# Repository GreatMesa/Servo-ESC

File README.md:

# Servo-ESC
Custom 4-Layer Board for better servo control.
Mainly uses I2C for IC communication & the analog pheripherials on the STM32F301
## Overview
This project stems from the want to replace the boards that normally control position on commercial servos.

The reason why I wanted to replace them is because 1, you can only control the position of the servo motors and not the velocity, let alone the torque. Also, you cannot get any useful feedback back from the servos, which means that you cannot get the current or temperature of the board, which could be useful for looking at possible faults / seeing the current overall power consumption.

With these Servo ESC's, you can communicate to the board using I2C, which allows to send the wanted position, velocity, and torque, while also communicating back the current position, velocity, torque, power consumption, and board temperature. This allows for a much higher view into what is happening in the board while also giving the servo greater precision.

## Board Schematic

## PCB Layout

## 3D Model

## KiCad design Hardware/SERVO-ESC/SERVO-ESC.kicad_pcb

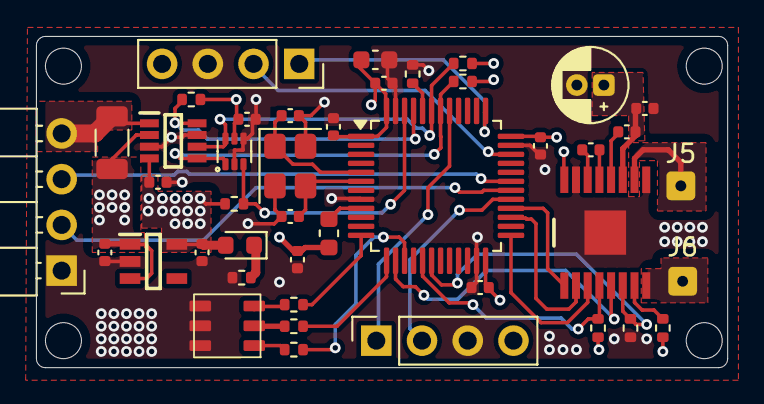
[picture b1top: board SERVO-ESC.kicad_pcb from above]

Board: 4 copper layers, 38.4 x 18.4 mm, 43 parts (0 on the bottom side), 37 nets.

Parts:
C1, C2, C3, C4, C9, C10, C15: 100nF; C_0402_1005Metric
C5: 4.7uF; C_0603_1608Metric
C6, C8, C12: 1uF; C_0402_1005Metric
C7: 22nF; C_0402_1005Metric
C11: 22uF; CP_Radial_D4.0mm_P1.50mm
C13, C14: 30pF; C_0402_1005Metric
C16: 10nF; C_0402_1005Metric
D1: LED; LED_0603_1608Metric
FB1: FerriteBead; L_0603_1608Metric
IC1: AP2112K; SOT95P285X140-5N
IC2: DRV8876PWPR; SOP65P640X120-17N
IC4: TMP102xxDRL; SOT-563
IC5: INA236AIDDFR; SOP65P280X110-8N
J1: Conn_01x04_Pin; PinHeader_1x04_P2.54mm_Horizontal
J2, J4: Conn_01x04_Pin; PinSocket_1x04_P2.54mm_Vertical
J5: +; SolderWire-0.1sqmm_1x01_D0.4mm_OD1mm
J6: -; SolderWire-0.1sqmm_1x01_D0.4mm_OD1mm
LED1: Untitled_1
R1, R10: 10k; R_0402_1005Metric
R2, R3, R4: 220; R_0402_1005Metric
R5, R6, R12, R13: 4.7k; R_0402_1005Metric
R7: 1k; R_0402_1005Metric
R8: 62k; R_0402_1005Metric
R9: 8.25k; R_0402_1005Metric
R11: 0.01; R_1206_3216Metric
U1: STM32F301C8Tx; LQFP-48_7x7mm_P0.5mm
Y1: 25MHZ; Crystal_SMD_3225-4Pin_3.2x2.5mm

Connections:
+3.3V: C1.1, C2.1, C3.1, C4.1, C5.1, C8.1, C12.1, C15.1, C16.1, D1.2 (A), FB1.2, IC1.5 (VOUT), IC2.16 (PMODE), IC4.5 (V+), IC5.4 (VS), J2.4, J4.4, R5.1, R6.1, R8.2, R10.1, R12.1, R13.1, U1.1 (VBAT), U1.24 (VDD), U1.36 (VDD), U1.48 (VDD)
+3.3VA: FB1.1, U1.9 (VDDA)
+7V: C6.1, C9.1, C10.1, C11.1, IC1.1 (VIN), IC1.3 (EN), IC2.11 (VM), IC5.2 (IN-), R11.2
+SV: IC5.1 (IN+), J1.4, R11.1
CPH: C7.2, IC2.13 (CPH)
CPL: C7.1, IC2.14 (CPL)
GND: C1.2, C2.2, C3.2, C4.2, C5.2, C6.2, C8.2, C9.2, C11.2, C12.2, C13.2, C14.2, C15.2, C16.2, IC1.2 (GND), IC2.9 (PGND), IC2.15 (GND), IC2.17 (EP), IC4.2 (GND), IC4.4 (ADD0), IC5.3 (GND), IC5.7 (A0), J1.1, J2.3, J4.3, LED1.1, LED1.2, LED1.3, R1.1, R7.2, R9.2, U1.8 (VSSA), U1.23 (VSS), U1.35 (VSS), U1.47 (VSS), Y1.2, Y1.4
HBRIDGE+: IC2.8 (OUT1), J6.1
HBRIDGE-: IC2.10 (OUT2), J5.1
HBRIDGE-FAULT: IC2.4 (NFAULT), R8.1, U1.17 (PA7)
HBRIDGE-IMODE: IC2.7 (IMODE), R10.2
HBRIDGE-IN1: IC2.1 (EN/IN1), U1.28 (PB15)
HBRIDGE-IN2: IC2.2 (PH/IN2), U1.27 (PB14)
HBRIDGE-IPROPI: IC2.6 (IPROPI), R9.1, U1.18 (PB0)
HBRIDGE-SLEEP: IC2.3 (NSLEEP), U1.25 (PB12)
HBRIDGE-VREF: IC2.5 (VREF), U1.14 (PA4)
HSE-IN: C13.1, U1.5 (PF0), Y1.1
HSE-OUT: C14.1, U1.6 (PF1), Y1.3
I2C-SCL-1: IC4.1 (SCL), IC5.5 (SCL), R5.2, U1.42 (PB6)
I2C-SCL-3: J4.2, U1.29 (PA8)
I2C-SDA-1: IC4.6 (SDA), IC5.6 (SDA), R6.2, U1.43 (PB7)
I2C-SDA-3: J4.1, U1.41 (PB5)
INA236-INT: IC5.8 (~ALERT), R12.2, U1.45 (PB8)
unnamed: D1.1 (K), R7.1
unnamed: LED1.4, R2.1
unnamed: LED1.5, R3.1
unnamed: LED1.6, R4.1
unnamed: R1.2, U1.44 (BOOT0)
RGB-LED-BLUE: R4.2, U1.12 (PA2)
RGB-LED-GREEN: R3.2, U1.13 (PA3)
RGB-LED-RED: R2.2, U1.15 (PA5)
SWCLK: J2.1, U1.37 (PA14)
SWDIO: J2.2, U1.34 (PA13)
TMP102-INT: IC4.3 (ALERT), R13.2, U1.46 (PB9)
UART-RX: J1.3, U1.31 (PA10)
UART-TX: J1.2, U1.30 (PA9)
VCP: C10.2, IC2.12 (VCP)

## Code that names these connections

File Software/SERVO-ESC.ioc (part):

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Mcu.Name=STM32F301C(6-8)Tx
Mcu.Package=LQFP48
Mcu.UserName=STM32F301C8Tx
PA10.Mode=I2C
PA10.Signal=I2C2_SDA
PA13.Mode=Serial_Wire
PA13.Signal=SYS_JTMS-SWDIO
PA14.Mode=Serial_Wire
PA14.Signal=SYS_JTCK-SWCLK
PA2.GPIOParameters=GPIO_Label
PA2.GPIO_Label=RGB_LED_BLUE
PA2.Signal=S_TIM2_CH3
PA3.GPIOParameters=GPIO_Label
PA3.GPIO_Label=RGB_LED_GREEN
PA3.Signal=S_TIM2_CH4
PA4.GPIOParameters=GPIO_Label
PA4.GPIO_Label=HBRIDGE-VREF
PA4.Signal=COMP_DAC1_group
PA5.GPIOParameters=GPIO_Label
PA5.GPIO_Label=RGB_LED_RED
PA5.Signal=S_TIM2_CH1_ETR
PA7.GPIOParameters=GPIO_Label
PA7.GPIO_Label=HBRIDGE-FALUT
PA7.Signal=GPIO_Input
PA8.Mode=I2C
PA8.Signal=I2C3_SCL
PA9.Mode=I2C
PA9.Signal=I2C2_SCL
PB0.GPIOParameters=GPIO_Label
PB0.GPIO_Label=HBRIDGE-IPROPI
PB0.Mode=IN11-Single-Ended
PB0.Signal=ADC1_IN11
PB12.GPIOParameters=GPIO_Label
PB12.GPIO_Label=HBRIDGE-SLEEP
PB12.Signal=GPIO_Output
PB14.Signal=S_TIM15_CH1
PB15.Signal=S_TIM15_CH2
PB5.Mode=I2C
PB5.Signal=I2C3_SDA
PB6.Mode=I2C
PB6.Signal=I2C1_SCL
PB7.Mode=I2C
PB7.Signal=I2C1_SDA
PB8.GPIOParameters=GPIO_Label,GPIO_ModeDefaultEXTI
PB8.GPIO_Label=INA236_ALERT
PB8.GPIO_ModeDefaultEXTI=GPIO_MODE_IT_FALLING
PB8.Signal=GPXTI8
PB9.GPIOParameters=GPIO_Label
PB9.GPIO_Label=TMP102_ALERT
PB9.Signal=GPXTI9
PF0-OSC_IN.Mode=HSE-External-Oscillator
PF0-OSC_IN.Signal=RCC_OSC_IN
PF1-OSC_OUT.Mode=HSE-External-Oscillator
PF1-OSC_OUT.Signal=RCC_OSC_OUT
RCC.HSEPLLFreq_Value=12500000
RCC.HSE_VALUE=25000000
RCC.SYSCLKFreq_VALUE=25000000
RCC.SYSCLKSourceVirtual=RCC_SYSCLKSOURCE_PLLCLK
board=custom

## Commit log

2025-11-02 Added PCB Files
2026-01-02 New PCB Files
2026-03-17 New Commit
2026-03-18 New stuff
2026-03-18 Ediited MT6701 Driver
2026-03-24 New board files (messed up gnd via)
2026-03-25 worked on task structures for tmp102 and ina236
2026-03-27 Adding new task structures
2026-04-23 New software + motor moving.
